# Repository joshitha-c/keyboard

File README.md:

# Travel keyboard

NomadKeys is a compact mechanical keyboard that I designed for people who need a reliable keyboard while travelling. The idea behind this project was to create something that is small enough to carry in a backpack without giving up the feel of a mechanical keyboard.

The keyboard is built around the Raspberry Pi Pico (RP2040) and uses a standard keyboard matrix with 1N4148 diodes for reliable key scanning. An I²C GPIO expander is used to increase the number of available input pins, and a rotary encoder provides an extra control that can be programmed for different functions.

The hardware was designed in KiCad 8 and can be used with firmware such as QMK or KMK.

---

## Project Goals

The main goals of this project were to:

- Build a compact keyboard that is easy to carry while travelling.
- Reduce the number of GPIO pins required by using a keyboard matrix.
- Prevent ghosting by adding a diode to every switch.
- Include a rotary encoder for additional controls.
- Keep the design simple enough to assemble and modify.

---

## Features

- Raspberry Pi Pico (RP2040)
- Compact layout for travel
- Mechanical switches
- 6 × 20 keyboard matrix
- 1N4148 diode on every switch
- I²C GPIO expander
- Rotary encoder with push button
- USB connectivity

---

## Components

| Component | Quantity |
|----------|---------:|
| Raspberry Pi Pico | 1 |
| I²C GPIO Expander | 1 |
| Rotary Encoder | 1 |
| Mechanical Switches | Depends on layout |
| 1N4148 Diodes | One per switch |
| Custom PCB | 1 |

---

## Future Improvements

There are still a few things I would like to add in future revisions:

- Bluetooth support
- Rechargeable battery
- OLED display
- VIA/Vial compatibility
- RGB lighting

---

## Software

- KiCad
- Fusion 360

## About This Project

This keyboard was developed as a personal hardware project to explore keyboard design using the RP2040. It combines PCB design,cad project into a single project while focusing on creating a compact keyboard that is practical for travelling.
schematics:

pcb:

cad file:

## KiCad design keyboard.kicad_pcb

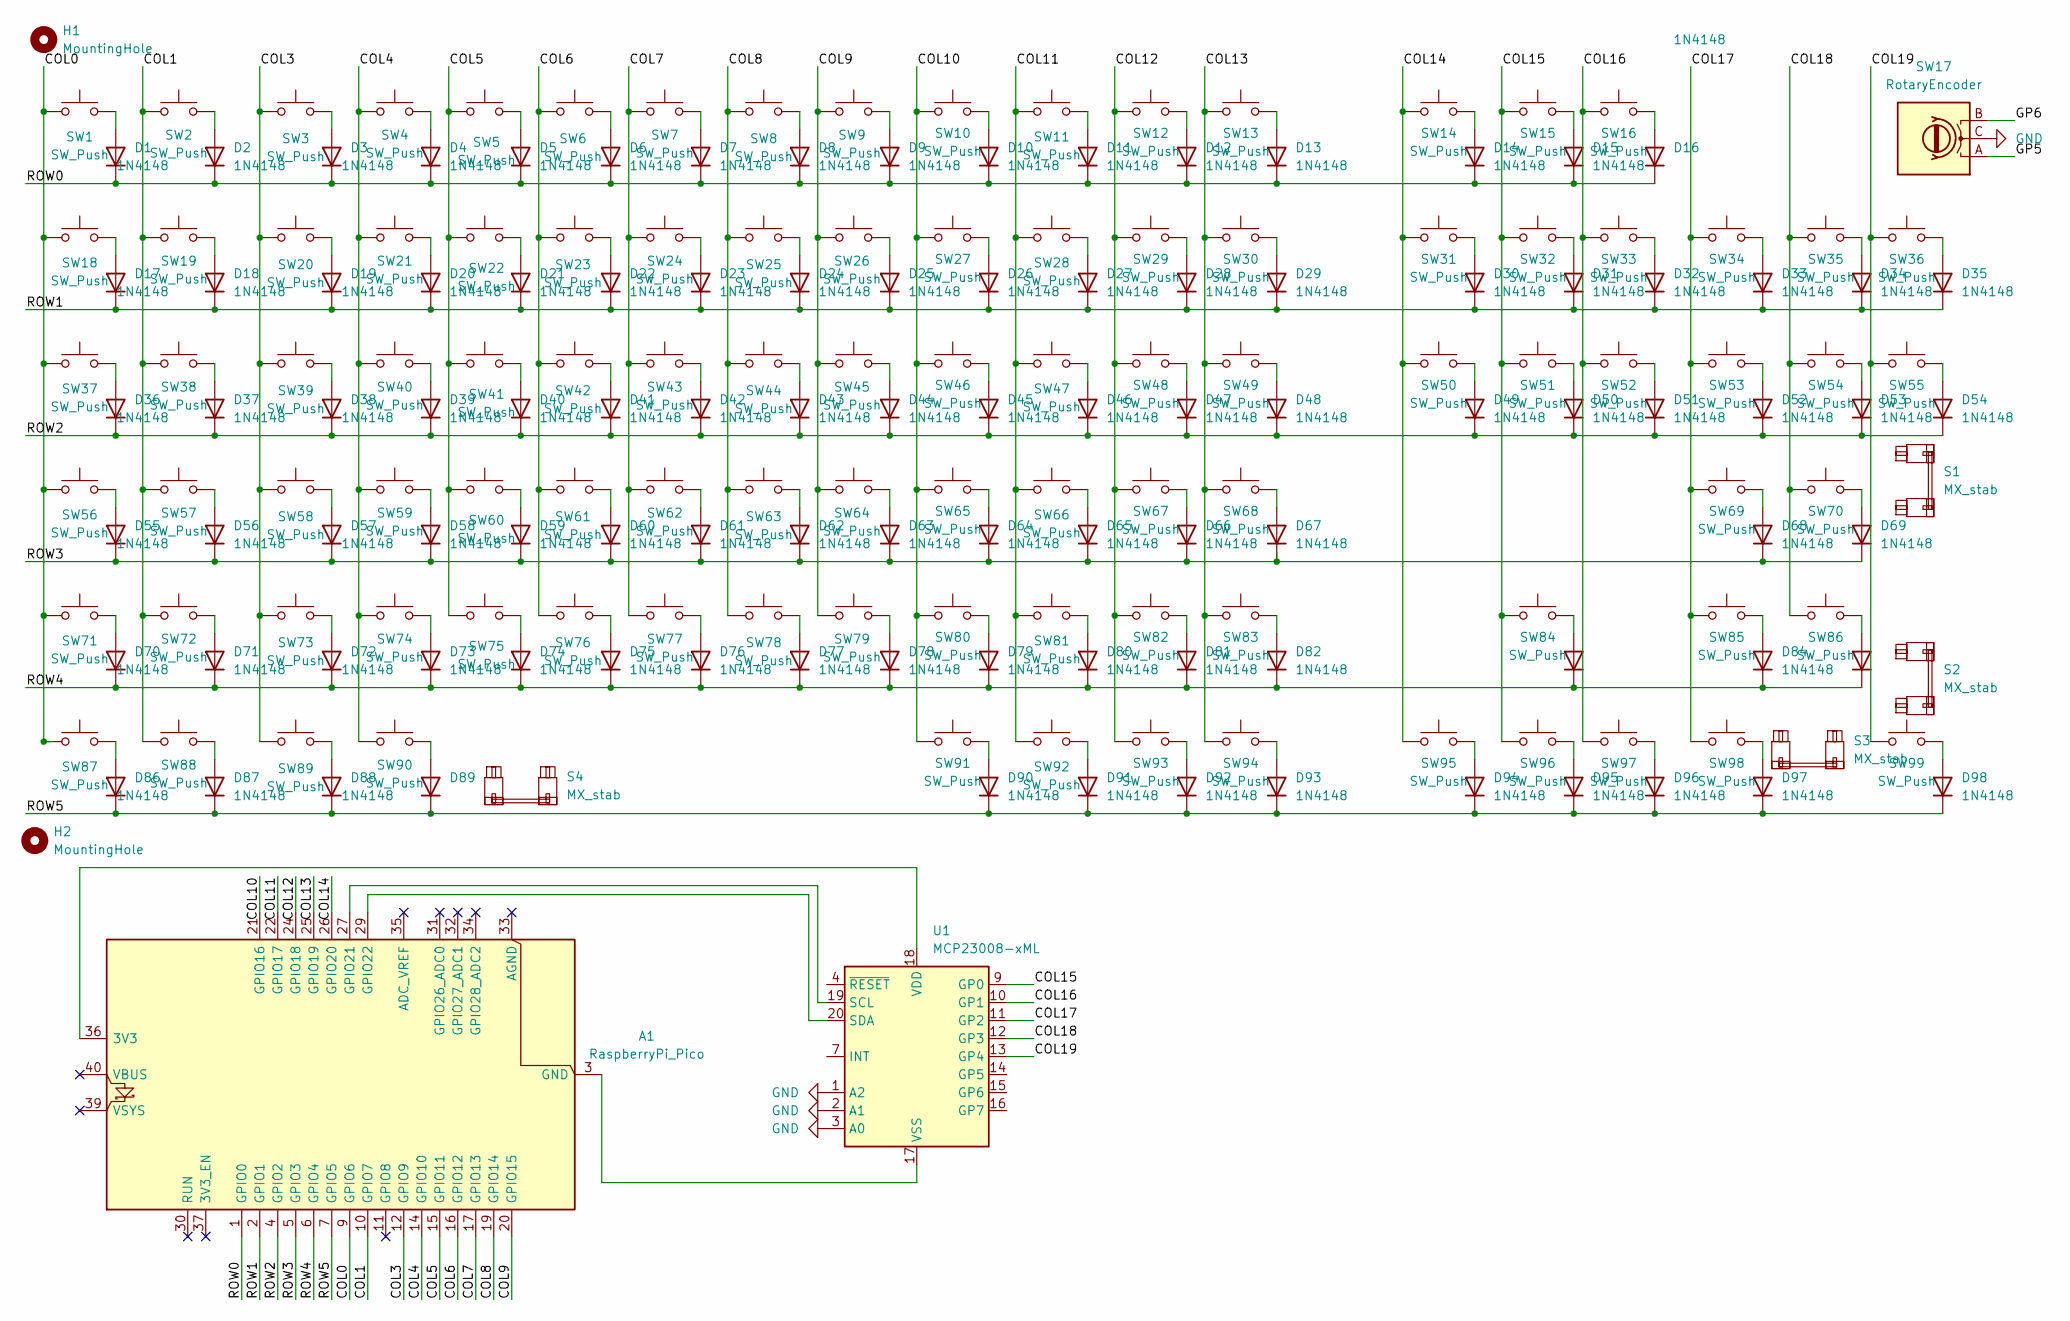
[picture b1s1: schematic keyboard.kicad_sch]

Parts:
A1: RaspberryPi_Pico; RaspberryPi_Pico_Common_THT
D1, D2, D3, D4, D5, D6, D7, D8, D9, D10, D11, D12, D13, D14, D15, D16, D17, D18, D19, D20, D21, D22, D23, D24, D25, D26, D27, D28, D29, D30, D31, D32, D33, D34, D35, D36, D37, D38, D39, D40, D41, D42, D43, D44, D45, D46, D47, D48, D49, D50, D51, D52, D53, D54, D55, D56, D57, D58, D59, D60, D61, D62, D63, D64, D65, D66, D67, D68, D69, D70, D71, D72, D73, D74, D75, D76, D77, D78, D79, D80, D81, D82, D83, D84, D85, D86, D87, D88, D89, D90, D91, D92, D93, D94, D95, D96, D97, D98: 1N4148; D_DO-35_SOD27_P7.62mm_Horizontal
H1, H2: MountingHole; MountingHole_3.2mm_M3
S1, S2, S3: MX_stab; STAB_MX_2u
S4: MX_stab; STAB_MX_6u
SW1, SW2, SW3, SW4, SW5, SW6, SW7, SW8, SW9, SW10, SW11, SW12, SW13, SW14, SW15, SW16, SW18, SW19, SW20, SW21, SW22, SW23, SW24, SW25, SW26, SW27, SW28, SW29, SW30, SW31, SW32, SW33, SW34, SW35, SW36, SW37, SW38, SW39, SW40, SW41, SW42, SW43, SW44, SW45, SW46, SW47, SW48, SW49, SW50, SW51, SW52, SW53, SW54, SW55, SW56, SW57, SW58, SW59, SW60, SW61, SW62, SW63, SW64, SW65, SW66, SW67, SW68, SW69, SW70, SW71, SW72, SW73, SW74, SW75, SW76, SW77, SW78, SW79, SW80, SW81, SW82, SW83, SW84, SW85, SW86, SW87, SW88, SW89, SW90, SW91, SW92, SW93, SW94, SW95, SW96, SW97, SW98, SW99: SW_Push; SW_MX_1u
SW17: RotaryEncoder; RotaryEncoder_Alps_EC11E_Vertical_H20mm
U1: MCP23008-xML; QFN-20-1EP_4x4mm_P0.5mm_EP2.7x2.7mm

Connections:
/COL0: A1.9 (GPIO6), SW1.1, SW18.1, SW37.1, SW56.1, SW71.1, SW87.1
/COL1: A1.10 (GPIO7), SW2.1, SW19.1, SW38.1, SW57.1, SW72.1, SW88.1
/COL3: A1.12 (GPIO9), SW3.1, SW20.1, SW39.1, SW58.1, SW73.1, SW89.1
/COL4: A1.14 (GPIO10), SW4.1, SW21.1, SW40.1, SW59.1, SW74.1, SW90.1
/COL5: A1.15 (GPIO11), SW5.1, SW22.1, SW41.1, SW60.1, SW75.1
/COL6: A1.16 (GPIO12), SW6.1, SW23.1, SW42.1, SW61.1, SW76.1
/COL7: A1.17 (GPIO13), SW7.1, SW24.1, SW43.1, SW62.1, SW77.1
/COL8: A1.19 (GPIO14), SW8.1, SW25.1, SW44.1, SW63.1, SW78.1
/COL9: A1.20 (GPIO15), SW9.1, SW26.1, SW45.1, SW64.1, SW79.1
/COL10: A1.21 (GPIO16), SW10.1, SW27.1, SW46.1, SW65.1, SW80.1, SW91.1
/COL11: A1.22 (GPIO17), SW11.1, SW28.1, SW47.1, SW66.1, SW81.1, SW92.1
/COL12: A1.24 (GPIO18), SW12.1, SW29.1, SW48.1, SW67.1, SW82.1, SW93.1
/COL13: A1.25 (GPIO19), SW13.1, SW30.1, SW49.1, SW68.1, SW83.1, SW94.1
/COL14: A1.26 (GPIO20), SW14.1, SW31.1, SW50.1, SW95.1
/COL15: SW15.1, SW32.1, SW51.1, SW84.1, SW96.1, U1.9 (GP0)
/COL16: SW16.1, SW33.1, SW52.1, SW97.1, U1.10 (GP1)
/COL17: SW34.1, SW53.1, SW69.1, SW85.1, SW98.1, U1.11 (GP2)
/COL18: SW35.1, SW54.1, SW70.1, SW86.1, U1.12 (GP3)
/COL19: SW36.1, SW55.1, SW99.1, U1.13 (GP4)
/GP5: SW17.A
/GP6: SW17.B
/ROW0: A1.1 (GPIO0), D1.1 (K), D2.1 (K), D3.1 (K), D4.1 (K), D5.1 (K), D6.1 (K), D7.1 (K), D8.1 (K), D9.1 (K), D10.1 (K), D11.1 (K), D12.1 (K), D13.1 (K), D14.1 (K), D15.1 (K), D16.1 (K)
/ROW1: A1.2 (GPIO1), D17.1 (K), D18.1 (K), D19.1 (K), D20.1 (K), D21.1 (K), D22.1 (K), D23.1 (K), D24.1 (K), D25.1 (K), D26.1 (K), D27.1 (K), D28.1 (K), D29.1 (K), D30.1 (K), D31.1 (K), D32.1 (K), D33.1 (K), D34.1 (K), D35.1 (K)
/ROW2: A1.4 (GPIO2), D36.1 (K), D37.1 (K), D38.1 (K), D39.1 (K), D40.1 (K), D41.1 (K), D42.1 (K), D43.1 (K), D44.1 (K), D45.1 (K), D46.1 (K), D47.1 (K), D48.1 (K), D49.1 (K), D50.1 (K), D51.1 (K), D52.1 (K), D53.1 (K), D54.1 (K)
/ROW3: A1.5 (GPIO3), D55.1 (K), D56.1 (K), D57.1 (K), D58.1 (K), D59.1 (K), D60.1 (K), D61.1 (K), D62.1 (K), D63.1 (K), D64.1 (K), D65.1 (K), D66.1 (K), D67.1 (K), D68.1 (K), D69.1 (K)
/ROW4: A1.6 (GPIO4), D70.1 (K), D71.1 (K), D72.1 (K), D73.1 (K), D74.1 (K), D75.1 (K), D76.1 (K), D77.1 (K), D78.1 (K), D79.1 (K), D80.1 (K), D81.1 (K), D82.1 (K), D83.1 (K), D84.1 (K), D85.1 (K)
/ROW5: A1.7 (GPIO5), D86.1 (K), D87.1 (K), D88.1 (K), D89.1 (K), D90.1 (K), D91.1 (K), D92.1 (K), D93.1 (K), D94.1 (K), D95.1 (K), D96.1 (K), D97.1 (K), D98.1 (K)
GND: SW17.C, U1.1 (A2), U1.2 (A1), U1.3 (A0)
unnamed: A1.36 (3V3), U1.18 (VDD)
unnamed: A1.27 (GPIO21), U1.19 (SCL)
unnamed: A1.29 (GPIO22), U1.20 (SDA)
unnamed: D1.2 (A), SW1.2
unnamed: D2.2 (A), SW2.2
unnamed: D3.2 (A), SW3.2
unnamed: D4.2 (A), SW4.2
unnamed: D5.2 (A), SW5.2
unnamed: D6.2 (A), SW6.2
unnamed: D7.2 (A), SW7.2
unnamed: D8.2 (A), SW8.2
unnamed: D9.2 (A), SW9.2
unnamed: D10.2 (A), SW10.2
unnamed: D11.2 (A), SW11.2
unnamed: D12.2 (A), SW12.2
unnamed: D13.2 (A), SW13.2
unnamed: D14.2 (A), SW14.2
unnamed: D15.2 (A), SW15.2
unnamed: D16.2 (A), SW16.2
unnamed: D17.2 (A), SW18.2
unnamed: D18.2 (A), SW19.2
unnamed: D19.2 (A), SW20.2
unnamed: D20.2 (A), SW21.2
unnamed: D21.2 (A), SW22.2
unnamed: D22.2 (A), SW23.2
unnamed: D23.2 (A), SW24.2
unnamed: D24.2 (A), SW25.2
unnamed: D25.2 (A), SW26.2
unnamed: D26.2 (A), SW27.2
unnamed: D27.2 (A), SW28.2
unnamed: D28.2 (A), SW29.2
unnamed: D29.2 (A), SW30.2
unnamed: D30.2 (A), SW31.2
unnamed: D31.2 (A), SW32.2
unnamed: D32.2 (A), SW33.2
unnamed: D33.2 (A), SW34.2
unnamed: D34.2 (A), SW35.2
unnamed: D35.2 (A), SW36.2
unnamed: D36.2 (A), SW37.2
unnamed: D37.2 (A), SW38.2
unnamed: D38.2 (A), SW39.2
unnamed: D39.2 (A), SW40.2
unnamed: D40.2 (A), SW41.2
unnamed: D41.2 (A), SW42.2
unnamed: D42.2 (A), SW43.2
unnamed: D43.2 (A), SW44.2
unnamed: D44.2 (A), SW45.2
unnamed: D45.2 (A), SW46.2
unnamed: D46.2 (A), SW47.2
unnamed: D47.2 (A), SW48.2
unnamed: D48.2 (A), SW49.2
unnamed: D49.2 (A), SW50.2
unnamed: D50.2 (A), SW51.2
unnamed: D51.2 (A), SW52.2
unnamed: D52.2 (A), SW53.2
unnamed: D53.2 (A), SW54.2
unnamed: D54.2 (A), SW55.2
unnamed: D55.2 (A), SW56.2
unnamed: D56.2 (A), SW57.2
unnamed: D57.2 (A), SW58.2
unnamed: D58.2 (A), SW59.2
unnamed: D59.2 (A), SW60.2
unnamed: D60.2 (A), SW61.2
unnamed: D61.2 (A), SW62.2
unnamed: D62.2 (A), SW63.2
unnamed: D63.2 (A), SW64.2
unnamed: D64.2 (A), SW65.2
unnamed: D65.2 (A), SW66.2
unnamed: D66.2 (A), SW67.2
unnamed: D67.2 (A), SW68.2
unnamed: D68.2 (A), SW69.2
unnamed: D69.2 (A), SW70.2
unnamed: D70.2 (A), SW71.2
unnamed: D71.2 (A), SW72.2
unnamed: D72.2 (A), SW73.2
unnamed: D73.2 (A), SW74.2
unnamed: D74.2 (A), SW75.2
unnamed: D75.2 (A), SW76.2
unnamed: D76.2 (A), SW77.2
unnamed: D77.2 (A), SW78.2
unnamed: D78.2 (A), SW79.2
unnamed: D79.2 (A), SW80.2
unnamed: D80.2 (A), SW81.2
unnamed: D81.2 (A), SW82.2
unnamed: D82.2 (A), SW83.2
unnamed: D83.2 (A), SW84.2
unnamed: D84.2 (A), SW85.2
unnamed: D85.2 (A), SW86.2
unnamed: D86.2 (A), SW87.2
unnamed: D87.2 (A), SW88.2
unnamed: D88.2 (A), SW89.2
unnamed: D89.2 (A), SW90.2
unnamed: D90.2 (A), SW91.2
unnamed: D91.2 (A), SW92.2
unnamed: D92.2 (A), SW93.2
unnamed: D93.2 (A), SW94.2
unnamed: D94.2 (A), SW95.2
unnamed: D95.2 (A), SW96.2
unnamed: D96.2 (A), SW97.2
unnamed: D97.2 (A), SW98.2
unnamed: D98.2 (A), SW99.2
unnamed: A1.3 (GND), A1.8 (GND), A1.13 (GND), A1.18 (GND), A1.23 (GND), A1.28 (GND), A1.38 (GND), U1.17 (VSS)

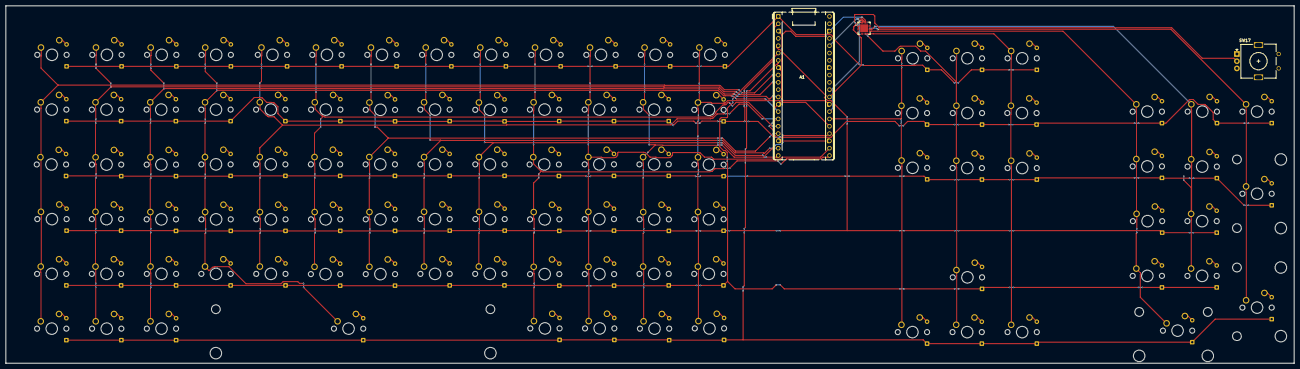
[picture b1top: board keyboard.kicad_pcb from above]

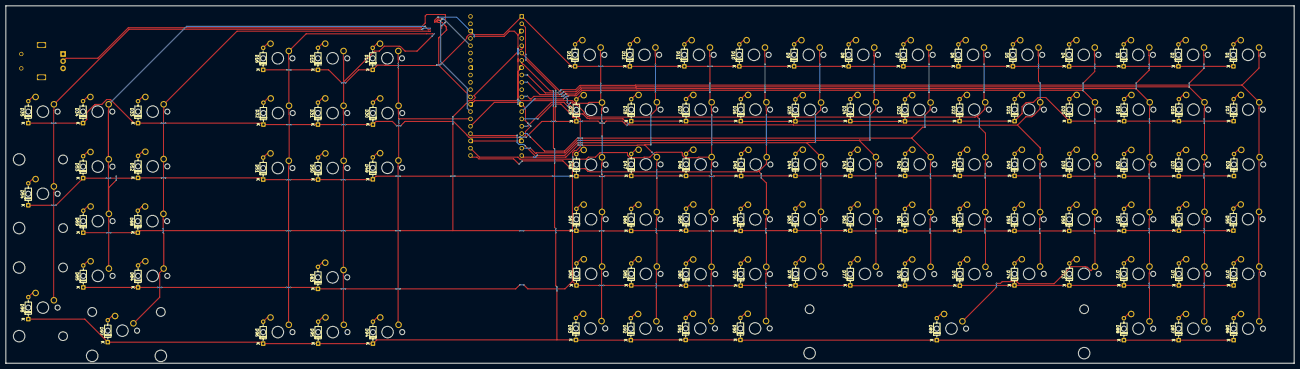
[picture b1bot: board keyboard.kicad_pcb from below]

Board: 2 copper layers, 447.0 x 124.0 mm, 203 parts (98 on the bottom side), 128 nets.
